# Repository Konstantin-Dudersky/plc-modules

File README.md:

Схемы простейших модулей для подключения к контроллеру по шине I2C.

Схемы разработаны в KiCad.

Документация - см. [docs/plc-modules.pdf]

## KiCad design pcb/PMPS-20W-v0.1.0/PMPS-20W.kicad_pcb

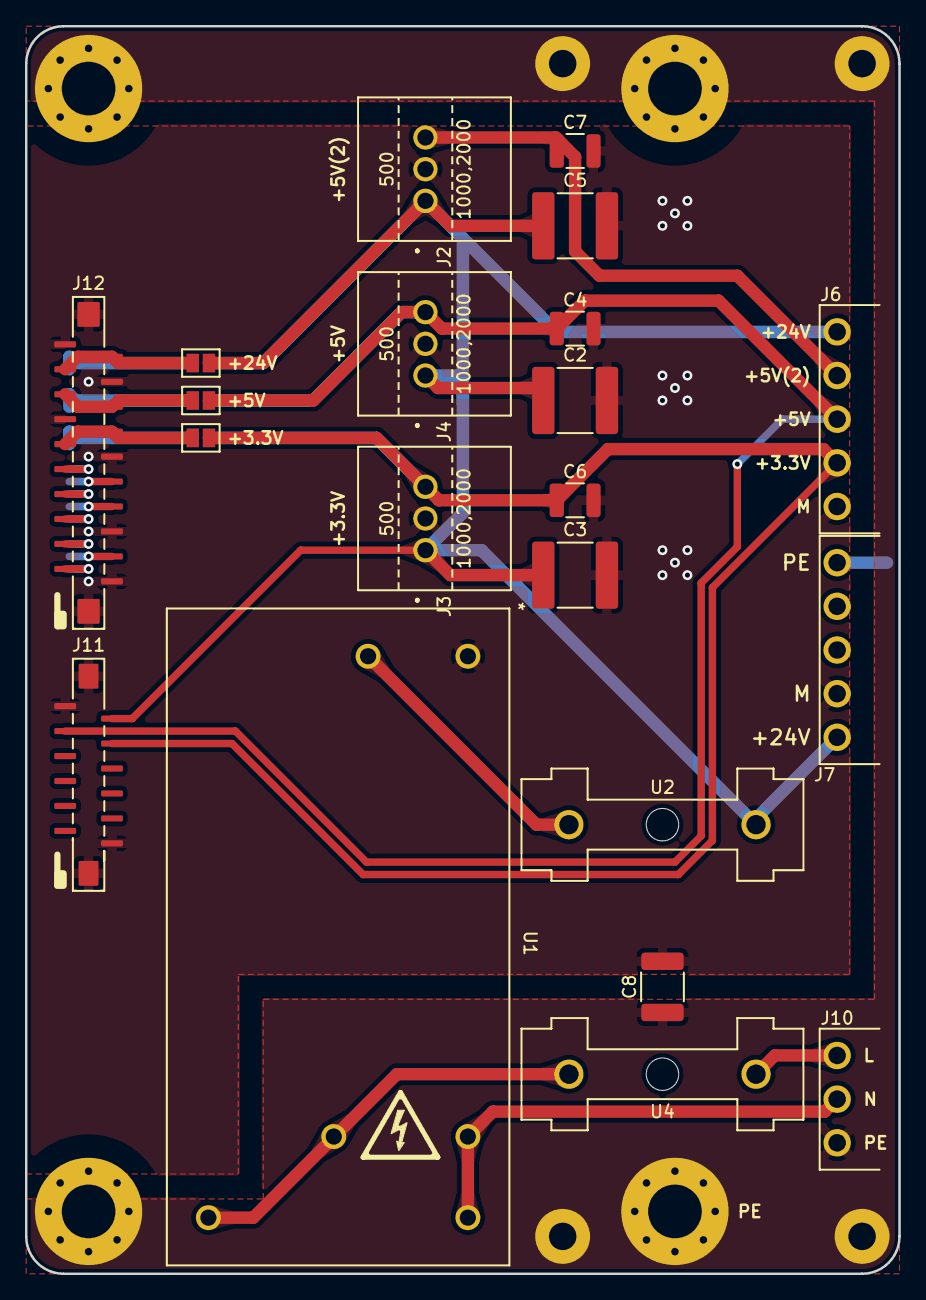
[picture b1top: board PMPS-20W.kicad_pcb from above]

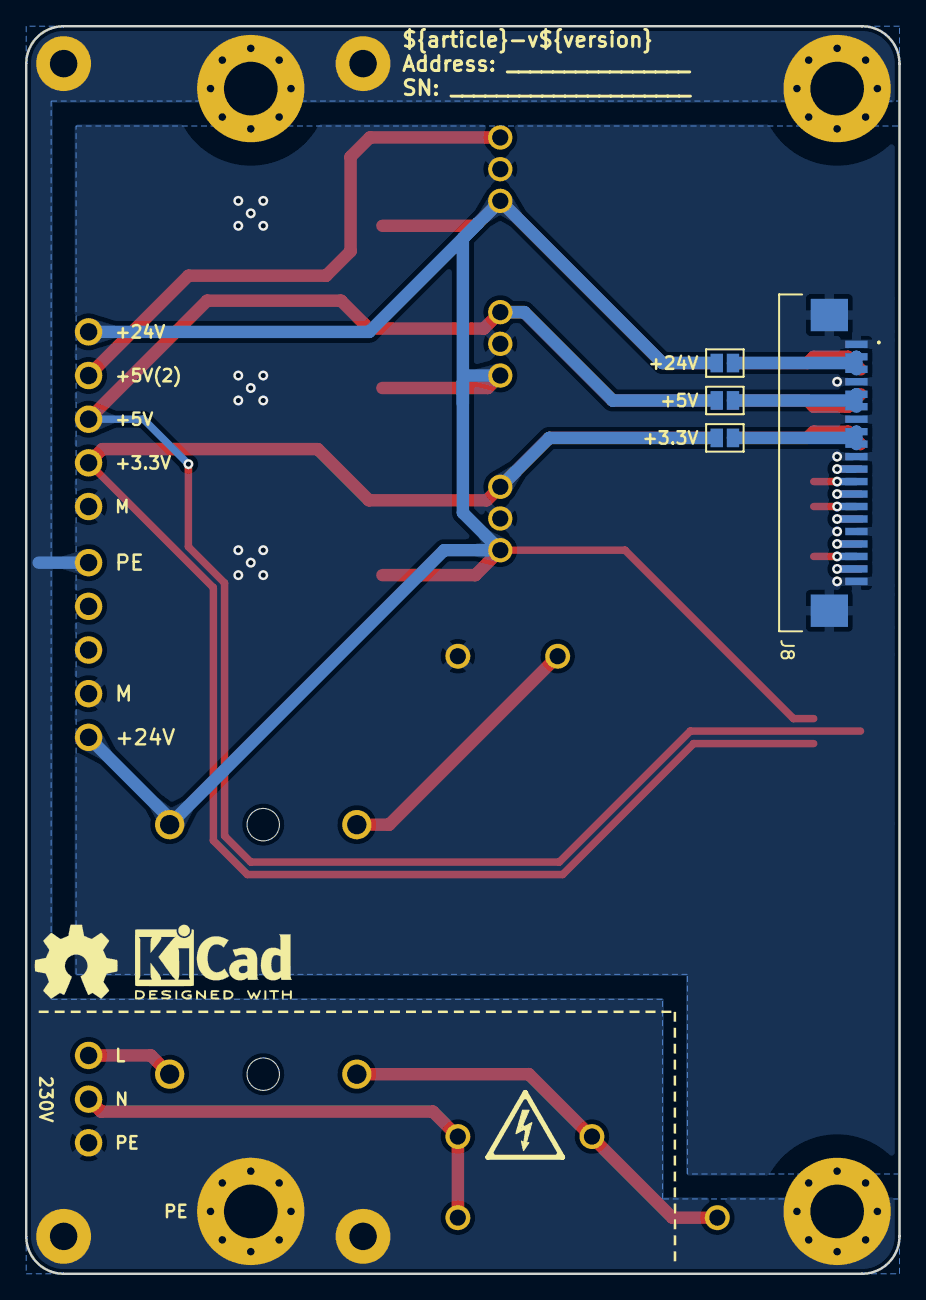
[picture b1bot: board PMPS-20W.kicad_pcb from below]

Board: 2 copper layers, 70.0 x 100.0 mm, 32 parts (6 on the bottom side), 24 nets.

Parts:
C2, C3, C5: 22uF; C_2220_5750Metric
C4, C6, C7: 22uF; C_1210_3225Metric
C8: 4.7nF 2kV; C_1812_4532Metric
H1, H2, H3, H4: M4; MountingHole_4.3mm_M4_Pad_Via
J2, J4: K7805-2000R3
J3: K7803-2000R3; K7805-2000R3
J6, J7: 15EDGRC-3.5-05P
J8: AFA07-S20FCC-00; AFA07S20FCA00
J10: 15EDGRC-3.5-03P
J11: AFA11-S12GLA-00
J12: AFA11-S20GLA-00
JP1, JP2, JP3, JP4, JP5, JP6: SolderJumper_2_Open; SolderJumper-2_P1.3mm_Open_Pad1.0x1.5mm
SP1: PMLED-xx-v0.0.3
U1: IRM-20-24; IRM-XX-24
U2, U4: 64900001039; 649-Series-Holder
kicad_logo: KiCad-Logo2_5mm_SilkScreen
oshw_logo: OSHW-Symbol_6.7x6mm_SilkScreen

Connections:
230V: J10.3, U4.1
+3V3: C6.1, J3.3 (+VO), J6.2, J11.4, JP3.2 (B), JP4.1 (A)
+3V3-IB-back: J8.8, J8.9, JP4.2 (B)
+3V3-IB-front: J12.8, J12.9, JP3.1 (A)
+5V: C4.1, J4.3 (+VO), J6.3, J11.3, JP1.2 (B), JP2.1 (A)
+5V(2): C7.1, J2.3 (+VO), J6.4
+5V-IB-back: J8.5, J8.6, JP2.2 (B)
+5V-IB-front: J12.5, J12.6, JP1.1 (A)
+24V: C2.1, C3.1, C5.1, J2.1 (VIN), J3.1 (VIN), J4.1 (VIN), J6.5, J7.1, J11.2, JP5.2 (B), JP6.1 (A), U2.2
+24V-IB-back: J8.2, J8.3, JP6.2 (B)
+24V-IB-front: J12.2, J12.3, JP5.1 (A)
/IBUS_CAN_GND: J8.13 (Pin_11), J12.13 (Pin_11)
/IBUS_CAN_H: J8.11, J12.11
/IBUS_CAN_L: J8.12 (Pin_11), J12.12 (Pin_11)
/IBUS_I2C_SCL: J8.15 (Pin_11), J12.15 (Pin_11)
/IBUS_I2C_SDA: J8.14 (Pin_11), J12.14 (Pin_11)
/IBUS_RST: J8.19 (Pin_11), J12.19 (Pin_11)
GND_MCU: C2.2, C3.2, C4.2, C5.2, C6.2, C7.2, C8.2, J2.2 (GND), J3.2 (GND), J4.2 (GND), J6.1, J7.2, J8.1, J8.4, J8.7, J8.10, J8.16 (Pin_11), J8.20 (Pin_11), J8.MP1 (Pin_11), J8.MP2 (Pin_11), J11.1, J11.12 (Pin_11), J11.MP1 (Pin_11), J11.MP2 (Pin_11), J12.1, J12.4, J12.7, J12.10, J12.16 (Pin_11), J12.20 (Pin_11), J12.MP1 (Pin_11), J12.MP2 (Pin_11), U1.1 (V-)
N: J10.2, U1.4 (AC/N)
unnamed: J8.17 (Pin_11), J12.17 (Pin_11)
unnamed: J8.18 (Pin_11), J12.18 (Pin_11)
unnamed: U1.3 (AC/L), U4.2
unnamed: U1.2 (V+), U2.1
PE: C8.1, H1.1 (1_1), H2.1 (1_1), H3.1 (1_1), H4.1 (1_1), J7.5, J10.1, SP1.PE (PE_PE)

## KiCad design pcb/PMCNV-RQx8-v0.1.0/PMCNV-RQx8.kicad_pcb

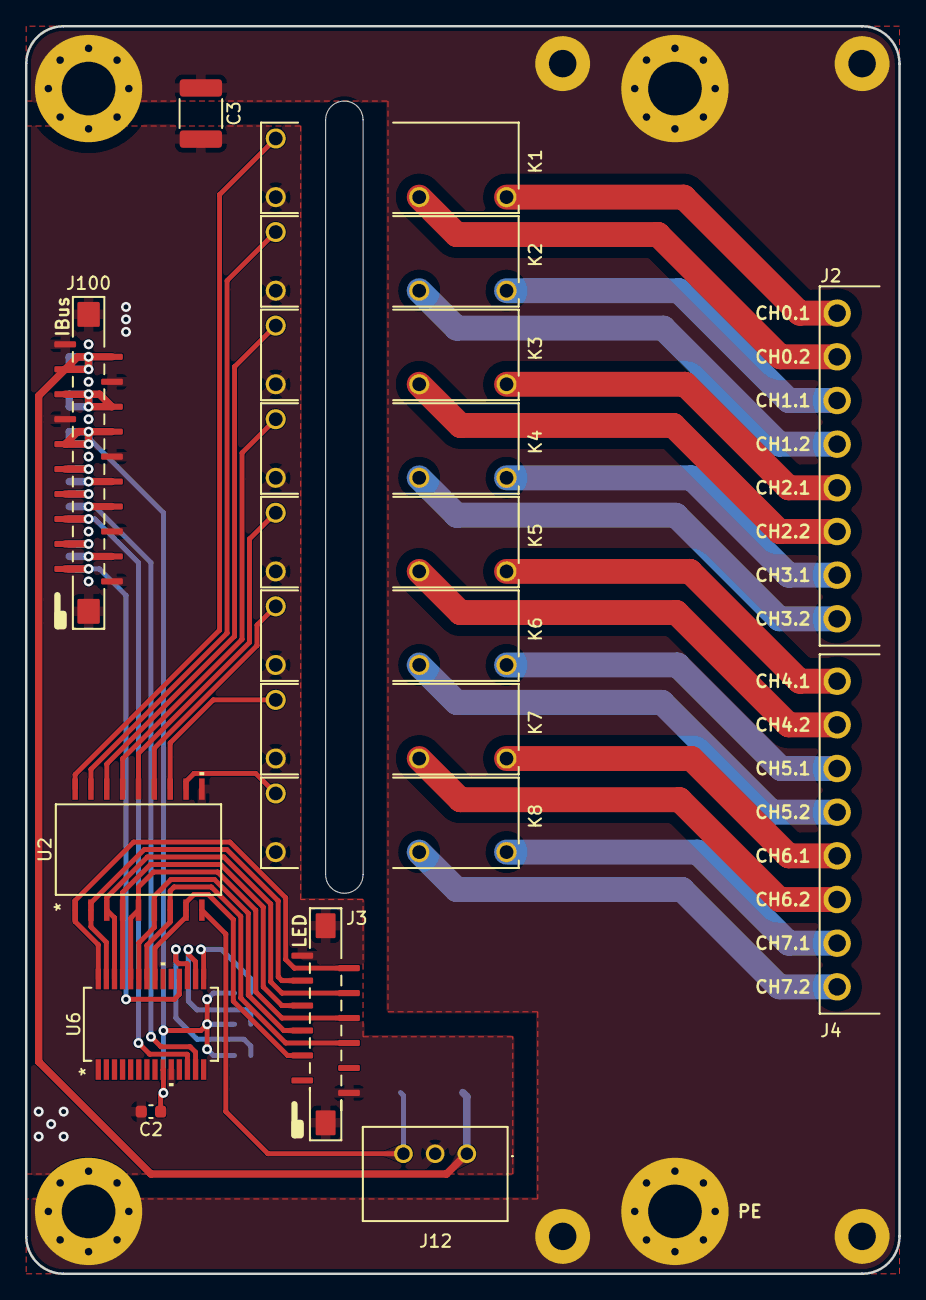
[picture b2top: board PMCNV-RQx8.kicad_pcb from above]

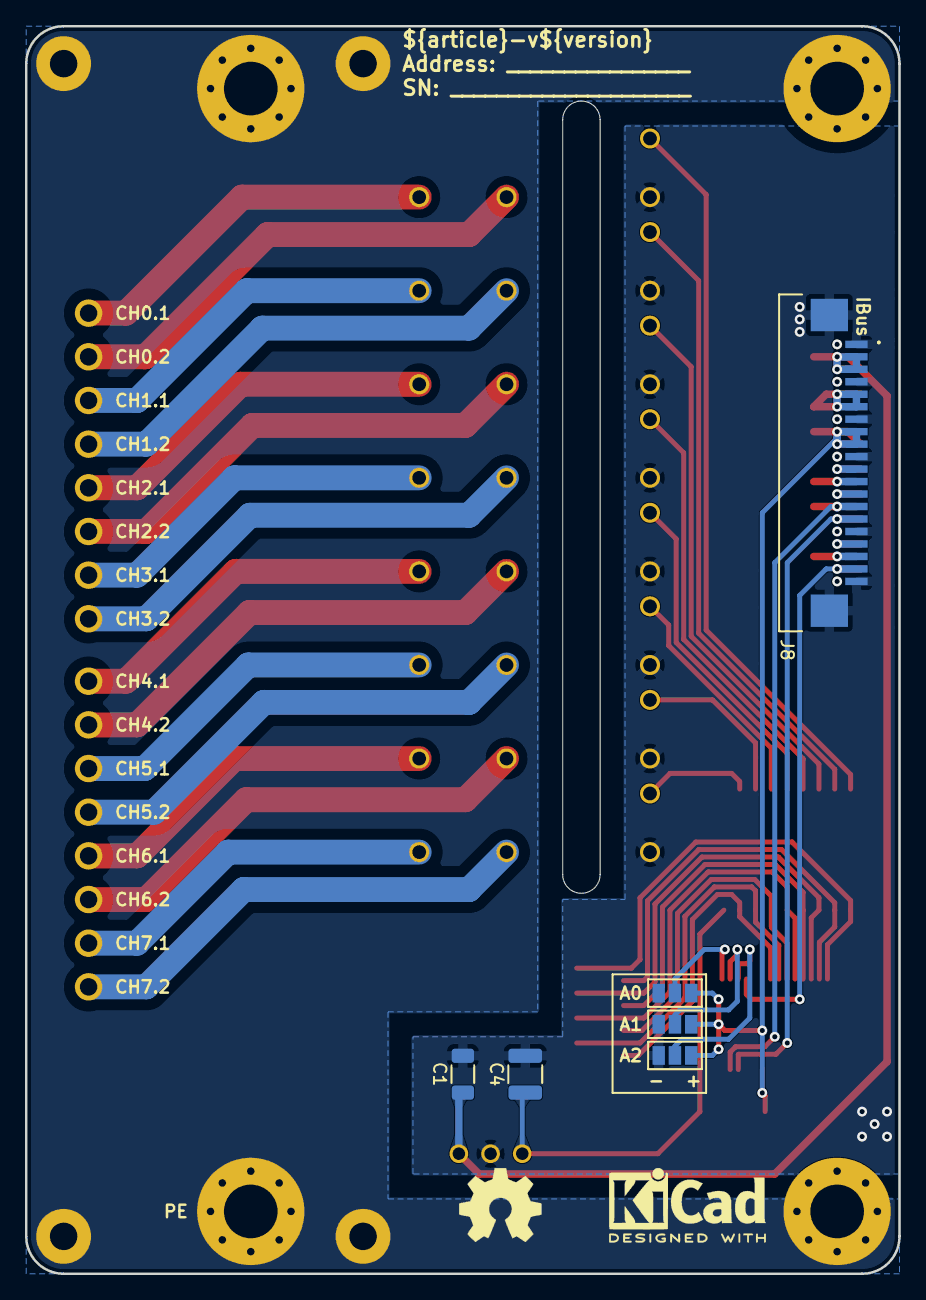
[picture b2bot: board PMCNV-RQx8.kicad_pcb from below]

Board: 2 copper layers, 70.0 x 100.0 mm, 30 parts (9 on the bottom side), 49 nets.

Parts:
C1: 10uF; C_1206_3216Metric
C2: 100nF; C_0603_1608Metric
C3: 4.7nF 2kV; C_1812_4532Metric
C4: 22uF; C_1210_3225Metric
H1, H2, H3, H4: M4; MountingHole_4.3mm_M4_Pad_Via
J2, J4: 15EDGRC-3.5-08P
J3: AFA07-S12FCC-00; AFA11-S12GLA-00
J8: AFA07-S20FCC-00; AFA07S20FCA00
J12: K7805-500R3; K7805500R3
J100: AFA11-S20GLA-00
JP5, JP6, JP7: SolderJumper_3_Open; SolderJumper-3_P1.3mm_Open_Pad1.0x1.5mm
K1, K2, K3, K4, K5, K6, K7, K8: G5NB-1A-E-DC5; G5NB-1A-E_DC12_RELAY_G5NB-1A_DC5_OMR
SP3: PMLED-xx-v0.0.3
U2: TBD62783AFG; SOP18-P-375-1p27_TOS-M
U6: MCP23017_SS; SSOP28_MC_MCH
kicad_logo: KiCad-Logo2_5mm_SilkScreen
oshw_logo: OSHW-Symbol_6.7x6mm_SilkScreen

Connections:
+5V: C4.1, J12.3 (+VO), U2.9 (VCC)
/A0: JP5.2 (C), U6.15 (A0)
/A1: JP6.2 (C), U6.16 (A1)
/A2: JP7.2 (C), U6.17 (A2)
/IBUS_5V: J8.5, J8.6, J100.5, J100.6
/IBUS_CAN_GND: J8.13 (Pin_11), J100.13 (Pin_11)
/IBUS_CAN_H: J8.11, J100.11
/IBUS_CAN_L: J8.12 (Pin_11), J100.12 (Pin_11)
/IBUS_I2C_SCL: J8.15 (Pin_11), J100.15 (Pin_11), U6.12 (SCL)
/IBUS_I2C_SDA: J8.14 (Pin_11), J100.14 (Pin_11), U6.13 (SDA)
/IBUS_RST: J8.19 (Pin_11), J100.19 (Pin_11), U6.18 (~RESET)
/K1: K1.4, U2.18 (O1)
/K1_exp: J3.2, U2.1 (I1), U6.28 (GPA7)
/K2: K2.4, U2.17 (O2)
/K2_exp: J3.3, U2.2 (I2), U6.27 (GPA6)
/K3: K3.4, U2.16 (O3)
/K3_exp: J3.4, U2.3 (I3), U6.26 (GPA5)
/K4: K4.4, U2.15 (O4)
/K4_exp: J3.5, U2.4 (I4), U6.25 (GPA4)
/K5: K5.4, U2.14 (O5)
/K5_exp: J3.6, U2.5 (I5), U6.24 (GPA3)
/K6: K6.4, U2.13 (O6)
/K6_exp: J3.7, U2.6 (I6), U6.23 (GPA2)
/K7: K7.4, U2.12 (O7)
/K7_exp: J3.8, U2.7 (I7), U6.22 (GPA1)
/K8: K8.4, U2.11 (O8)
/K8_exp: J3.9, U2.8 (I8), U6.21 (GPA0)
IBUS_3V3: C2.1, J8.8, J8.9, J100.8, J100.9, JP5.3 (B), JP6.3 (B), JP7.3 (B), U6.9 (VDD)
IBUS_24V: C1.1, J8.2, J8.3, J12.1 (VIN), J100.2, J100.3
IBUS_GND: C1.2, C2.2, C3.2, C4.2, J3.1, J3.12 (Pin_11), J3.MP1 (Pin_11), J3.MP2 (Pin_11), J8.1, J8.4, J8.7, J8.10, J8.16 (Pin_11), J8.20 (Pin_11), J8.MP1 (Pin_11), J8.MP2 (Pin_11), J12.2 (GND), J100.1, J100.4, J100.7, J100.10, J100.16 (Pin_11), J100.20 (Pin_11), J100.MP1 (Pin_11), J100.MP2 (Pin_11), JP5.1 (A), JP6.1 (A), JP7.1 (A), K1.1, K2.1, K3.1, K4.1, K5.1, K6.1, K7.1, K8.1, U2.10 (GND), U6.10 (VSS)
unnamed: J2.1, K4.2
unnamed: J2.2, K4.3
unnamed: J2.3, K3.2
unnamed: J2.4, K3.3
unnamed: J2.5, K2.2
unnamed: J2.6, K2.3
unnamed: J2.7, K1.2
unnamed: J2.8, K1.3
unnamed: J4.1, K8.2
unnamed: J4.2, K8.3
unnamed: J4.3, K7.2
unnamed: J4.4, K7.3
unnamed: J4.5, K6.2
unnamed: J4.6, K6.3
unnamed: J4.7, K5.2
unnamed: J4.8, K5.3
unnamed: J8.17 (Pin_11), J100.17 (Pin_11)
unnamed: J8.18 (Pin_11), J100.18 (Pin_11)
PE: C3.1, H1.1 (1_1), H2.1 (1_1), H3.1 (1_1), H4.1 (1_1), SP3.PE (PE_PE)

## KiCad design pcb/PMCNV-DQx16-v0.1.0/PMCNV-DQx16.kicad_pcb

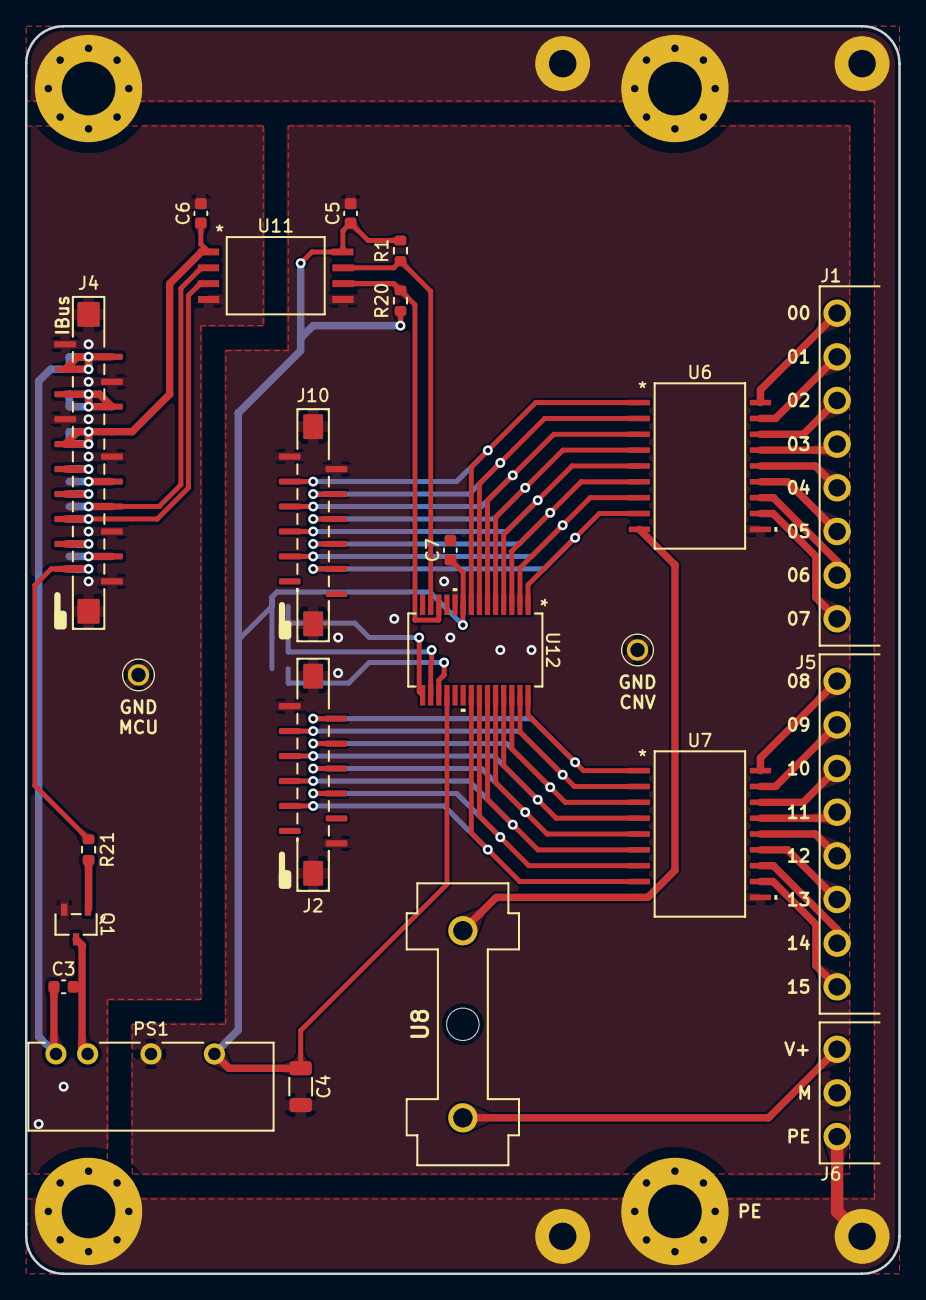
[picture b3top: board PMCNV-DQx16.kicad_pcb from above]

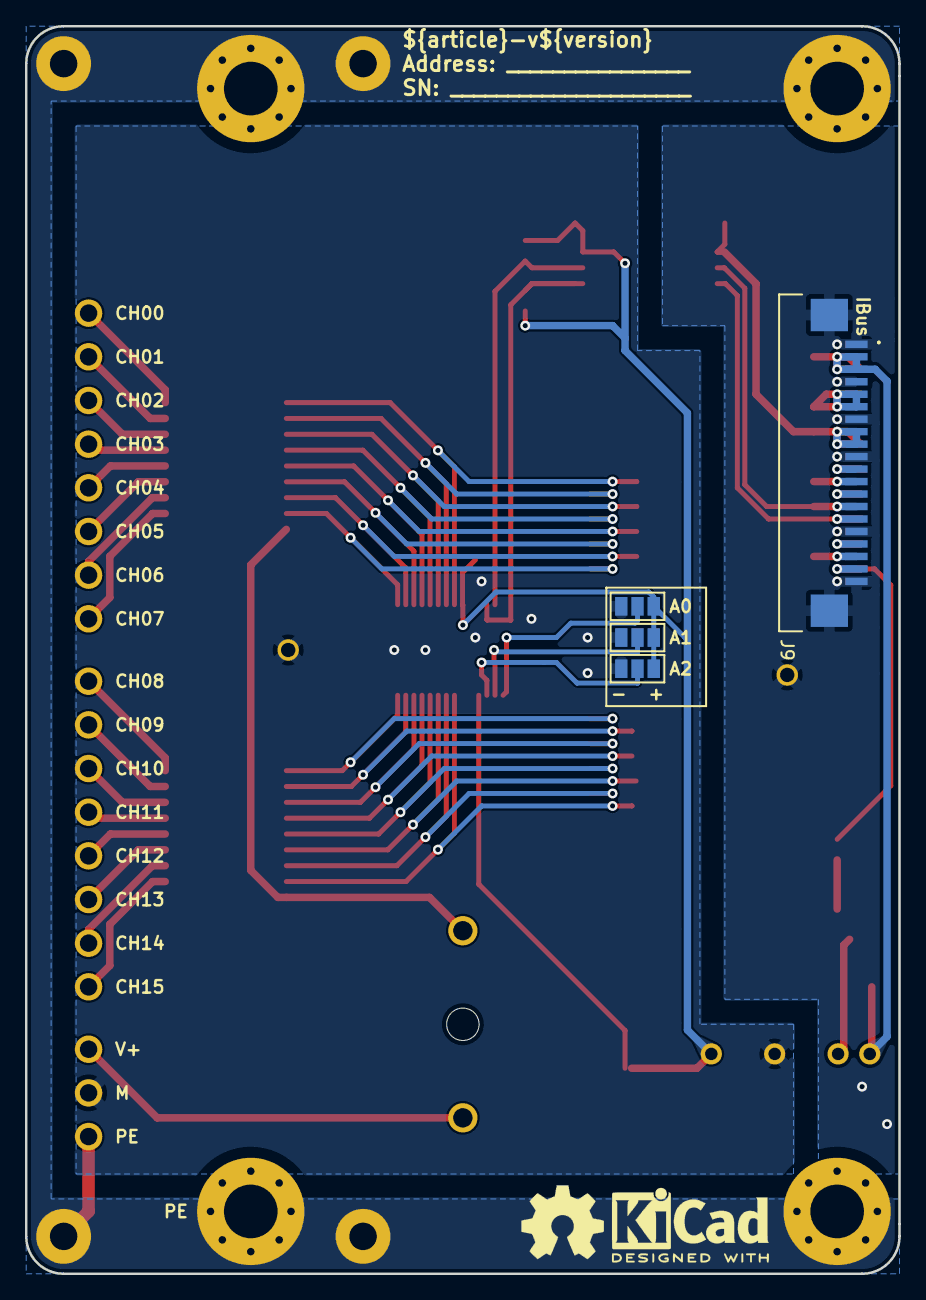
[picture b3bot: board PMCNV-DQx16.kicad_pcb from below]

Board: 2 copper layers, 70.0 x 100.0 mm, 34 parts (6 on the bottom side), 56 nets.

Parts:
C3: 1uF; C_0603_1608Metric
C4: 10uF; C_1206_3216Metric
C5, C6, C7: 100nF; C_0603_1608Metric
H1, H2, H3, H4: M4; MountingHole_4.3mm_M4_Pad_Via
J1, J5: 15EDGRC-3.5-08P
J2, J10: AFA11-S12GLA-00
J4: AFA11-S20GLA-00
J6: 15EDGRC-3.5-03P
J9: AFA07-S20FCC-00; AFA07S20FCA00
JP5, JP6, JP7: SolderJumper_3_Open; SolderJumper-3_P1.3mm_Open_Pad1.0x1.5mm
PS1: 24V/5V; B2405LS-1WR3
Q1: 2N7002K; 2N7002K_ONS
R1, R20: 3k3; R_0603_1608Metric
R21: 100R; R_0603_1608Metric
SP1: PMLED-xx-v0.0.3
U2, U5: 5117
U6, U7: TBD62783AFG; SOP18-P-375-1p27_TOS-M
U8: 64900001039; 649-Series-Holder
U11: CA-IS3021G; SOICW8_CLG
U12: MCP23017_SS; SSOP28_MC_MCH
kicad_logo: KiCad-Logo2_5mm_SilkScreen
oshw_logo: OSHW-Symbol_6.7x6mm_SilkScreen

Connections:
+5V_CNV: C4.1, C5.1, C7.1, JP5.3 (B), JP6.3 (B), JP7.3 (B), PS1.6 (+V), R1.1, R20.1, U11.8 (VDDb), U12.9 (VDD), U12.18 (~RESET)
+V: U6.9 (VCC), U7.9 (VCC), U8.2
/A0: JP5.2 (C), U12.15 (A0)
/A1: JP6.2 (C), U12.16 (A1)
/A2: JP7.2 (C), U12.17 (A2)
/CH00_in: J10.3, U6.1 (I1), U12.8 (GPB7)
/CH01_in: J10.4, U6.2 (I2), U12.7 (GPB6)
/CH02_in: J10.5, U6.3 (I3), U12.6 (GPB5)
/CH03_in: J10.6, U6.4 (I4), U12.5 (GPB4)
/CH04_in: J10.7, U6.5 (I5), U12.4 (GPB3)
/CH05_in: J10.8, U6.6 (I6), U12.3 (GPB2)
/CH06_in: J10.9, U6.7 (I7), U12.2 (GPB1)
/CH07_in: J10.10, U6.8 (I8), U12.1 (GPB0)
/CH08_in: J2.2, U7.1 (I1), U12.28 (GPA7)
/CH09_in: J2.3, U7.2 (I2), U12.27 (GPA6)
/CH10_in: J2.4, U7.3 (I3), U12.26 (GPA5)
/CH11_in: J2.5, U7.4 (I4), U12.25 (GPA4)
/CH12_in: J2.6, U7.5 (I5), U12.24 (GPA3)
/CH13_in: J2.7, U7.6 (I6), U12.23 (GPA2)
/CH14_in: J2.8, U7.7 (I7), U12.22 (GPA1)
/CH15_in: J2.9, U7.8 (I8), U12.21 (GPA0)
/IBUS_5V: J4.5, J4.6, J9.5, J9.6
/IBUS_CAN_GND: J4.13 (Pin_11), J9.13 (Pin_11)
/IBUS_CAN_H: J4.11, J9.11
/IBUS_CAN_L: J4.12 (Pin_11), J9.12 (Pin_11)
/IBUS_I2C_SCL: J4.15 (Pin_11), J9.15 (Pin_11), U11.3 (SCLa)
/IBUS_I2C_SDA: J4.14 (Pin_11), J9.14 (Pin_11), U11.2 (SDAa)
/IBUS_RST: J4.19 (Pin_11), J9.19 (Pin_11), R21.1
/SCL_CNV: R20.2, U11.6 (SCLb), U12.12 (SCK)
/SDA_CNV: R1.2, U11.7 (SDAb), U12.13 (SI)
/a.0_out: J1.8, U6.18 (O1)
/a.1_out: J1.7, U6.17 (O2)
/a.2_out: J1.6, U6.16 (O3)
/a.3_out: J1.5, U6.15 (O4)
/a.4_out: J1.4, U6.14 (O5)
/a.5_out: J1.3, U6.13 (O6)
/a.6_out: J1.2, U6.12 (O7)
/a.7_out: J1.1, U6.11 (O8)
/b.0_out: J5.8, U7.18 (O1)
/b.1_out: J5.7, U7.17 (O2)
/b.2_out: J5.6, U7.16 (O3)
/b.3_out: J5.5, U7.15 (O4)
/b.4_out: J5.4, U7.14 (O5)
/b.5_out: J5.3, U7.13 (O6)
/b.6_out: J5.2, U7.12 (O7)
/b.7_out: J5.1, U7.11 (O8)
GND_CNV: C4.2, C5.2, C7.2, J2.1, J2.12 (Pin_11), J2.MP1 (Pin_11), J2.MP2 (Pin_11), J6.2, J10.1, J10.2, J10.MP1 (Pin_11), J10.MP2 (Pin_11), JP5.1 (A), JP6.1 (A), JP7.1 (A), PS1.4 (0V), U5.1, U6.10 (GND), U7.10 (GND), U11.5 (GNDb), U12.10 (VSS)
IBUS_3V3: C6.1, J4.8, J4.9, J9.8, J9.9, U11.1 (VDDa)
IBUS_24V: C3.1, J4.2, J4.3, J9.2, J9.3, PS1.1 (Vin)
IBUS_GND: C6.2, J4.1, J4.4, J4.7, J4.10, J4.16 (Pin_11), J4.20 (Pin_11), J4.MP1 (Pin_11), J4.MP2 (Pin_11), J9.1, J9.4, J9.7, J9.10, J9.16 (Pin_11), J9.20 (Pin_11), J9.MP1 (Pin_11), J9.MP2 (Pin_11), Q1.2 (S), U2.1, U11.4 (GNDa)
unnamed: J4.17 (Pin_11), J9.17 (Pin_11)
unnamed: J4.18 (Pin_11), J9.18 (Pin_11)
unnamed: J6.3, U8.1
unnamed: C3.2, PS1.2 (GND), Q1.3 (D)
unnamed: Q1.1 (G), R21.2
PE: H1.1 (1_1), H2.1 (1_1), H3.1 (1_1), H4.1 (1_1), J6.1, SP1.PE (PE_PE)

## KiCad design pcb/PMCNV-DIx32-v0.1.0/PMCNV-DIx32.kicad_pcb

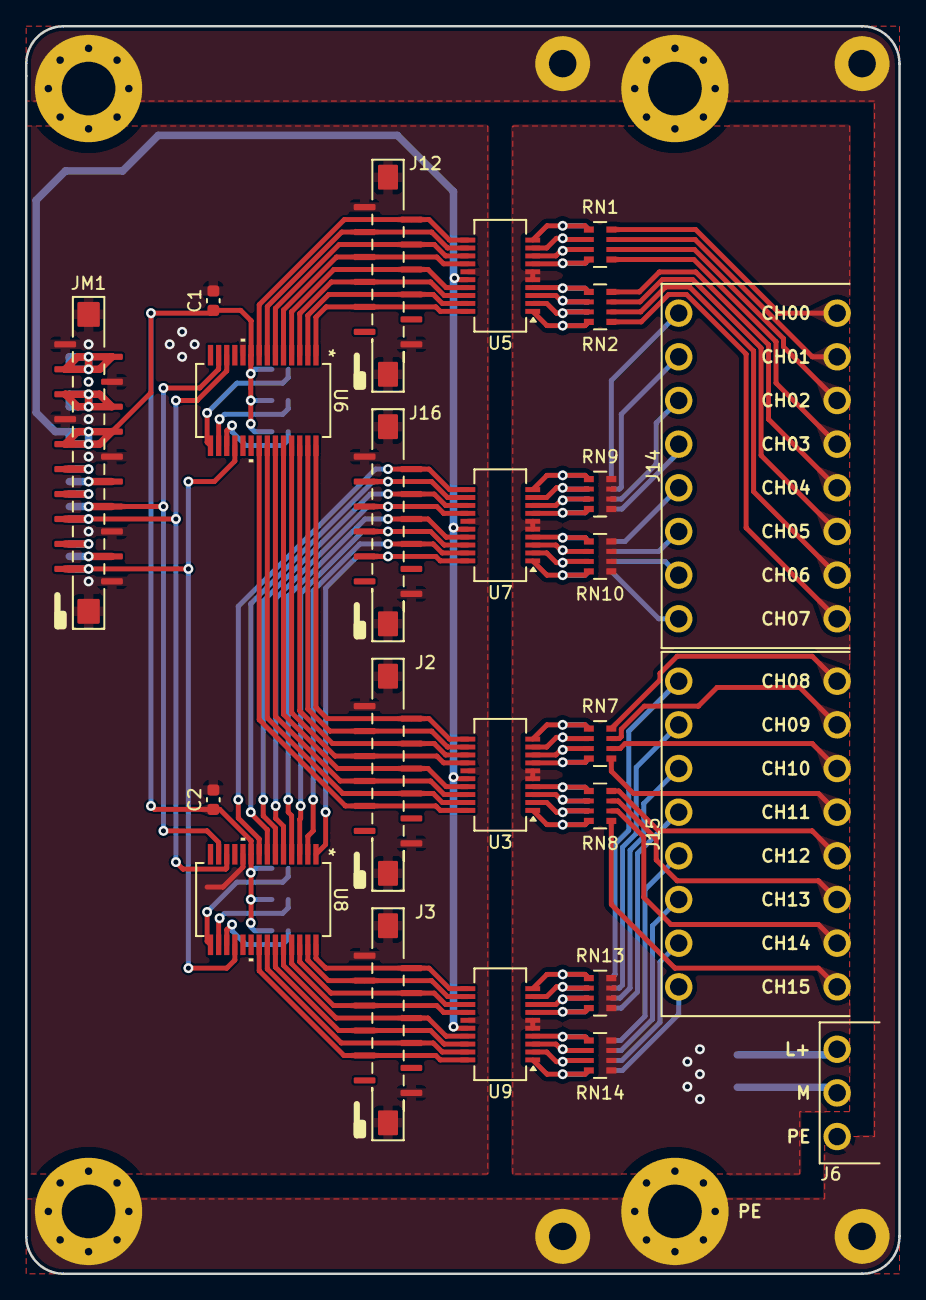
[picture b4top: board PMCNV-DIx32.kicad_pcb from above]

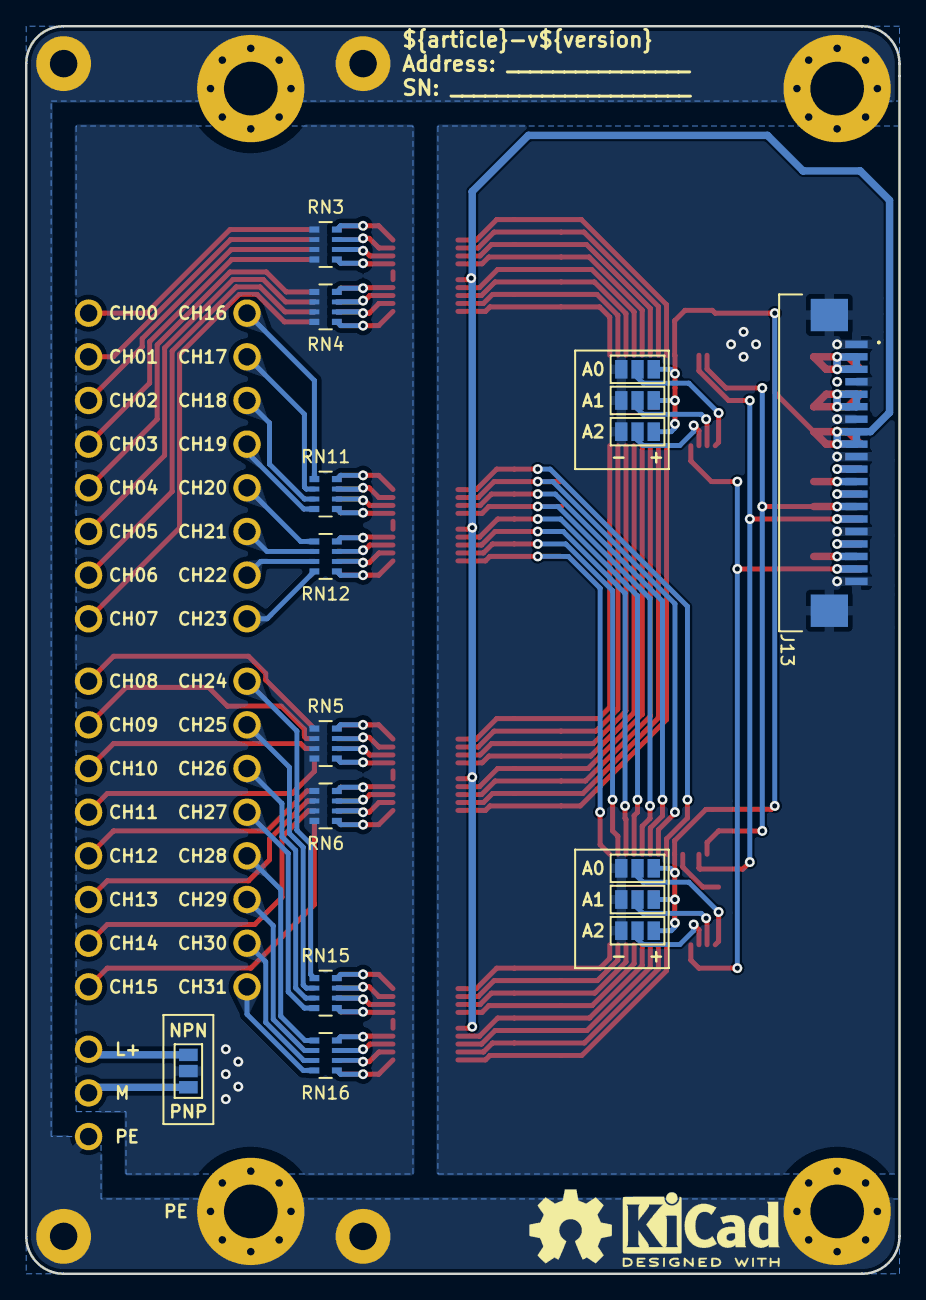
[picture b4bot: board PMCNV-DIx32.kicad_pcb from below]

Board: 2 copper layers, 70.0 x 100.0 mm, 47 parts (18 on the bottom side), 118 nets.

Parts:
C1, C2: 100nF; C_0603_1608Metric
H1, H2, H3, H4: M4; MountingHole_4.3mm_M4_Pad_Via
J2, J3, J12, J16: AFA07-S12FCC-00; AFA11-S12GLA-00
J6: 15EDGRC-3.5-05P; 15EDGRC-3.5-03P
J13: AFA07-S20FCC-00; AFA07S20FCA00
J14, J15: 15EDGRH-3.5-16P
JM1: AFA07-S20FCC-00; AFA11-S20GLA-00
JP5, JP6, JP7, JP8, JP9, JP10, JP11: SolderJumper_3_Open; SolderJumper-3_P1.3mm_Open_Pad1.0x1.5mm
RN1, RN2, RN7, RN8, RN11, RN12, RN15, RN16: 2k7; R_Array_Convex_4x0603
RN3, RN4, RN5, RN6, RN9, RN10, RN13, RN14: 750R; R_Array_Convex_4x0603
SP1: PMLED-xx-v0.0.3
U3, U5, U7, U9: CA-IS3980P; SSOP-20_3.9x8.7mm_P0.635mm
U6, U8: MCP23017_SS; SSOP28_MC_MCH
kicad_logo: KiCad-Logo2_5mm_SilkScreen
oshw_logo: OSHW-Symbol_6.7x6mm_SilkScreen

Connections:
/A0_0: JP5.2 (C), U6.15 (A0)
/A0_1: JP8.2 (C), U8.15 (A0)
/A1_0: JP6.2 (C), U6.16 (A1)
/A1_1: JP9.2 (C), U8.16 (A1)
/A2_0: JP7.2 (C), U6.17 (A2)
/A2_1: JP11.2 (C), U8.17 (A2)
/CH00: J12.2, U5.11 (B8), U6.8 (GPB7)
/CH00_div: RN1.1 (R1.1), RN3.4 (R4.1), U5.10 (A8)
/CH00_in: J14.8, RN1.8 (R1.2)
/CH01: J12.3, U5.12 (B7), U6.7 (GPB6)
/CH01_div: RN1.2 (R2.1), RN3.3 (R3.1), U5.9 (A7)
/CH01_in: J14.7, RN1.7 (R2.2)
/CH02: J12.4, U5.13 (B6), U6.6 (GPB5)
/CH02_div: RN1.3 (R3.1), RN3.2 (R2.1), U5.8 (A6)
/CH02_in: J14.6, RN1.6 (R3.2)
/CH03: J12.5, U5.14 (B5), U6.5 (GPB4)
/CH03_div: RN1.4 (R4.1), RN3.1 (R1.1), U5.7 (A5)
/CH03_in: J14.5, RN1.5 (R4.2)
/CH04: J12.6, U5.17 (B4), U6.4 (GPB3)
/CH04_div: RN2.1 (R1.1), RN4.4 (R4.1), U5.4 (A4)
/CH04_in: J14.4, RN2.8 (R1.2)
/CH05: J12.7, U5.18 (B3), U6.3 (GPB2)
/CH05_div: RN2.2 (R2.1), RN4.3 (R3.1), U5.3 (A3)
/CH05_in: J14.3, RN2.7 (R2.2)
/CH06: J12.8, U5.19 (B2), U6.2 (GPB1)
/CH06_div: RN2.3 (R3.1), RN4.2 (R2.1), U5.2 (A2)
/CH06_in: J14.2, RN2.6 (R3.2)
/CH07: J12.9, U5.20 (B1), U6.1 (GPB0)
/CH07_div: RN2.4 (R4.1), RN4.1 (R1.1), U5.1 (A1)
/CH07_in: J14.1, RN2.5 (R4.2)
/CH08: J2.2, U3.11 (B8), U6.28 (GPA7)
/CH08_div: RN5.4 (R4.1), RN7.1 (R1.1), U3.10 (A8)
/CH08_in: J15.8, RN7.8 (R1.2)
/CH09: J2.3, U3.12 (B7), U6.27 (GPA6)
/CH09_div: RN5.3 (R3.1), RN7.2 (R2.1), U3.9 (A7)
/CH09_in: J15.7, RN7.7 (R2.2)
/CH10: J2.4, U3.13 (B6), U6.26 (GPA5)
/CH10_div: RN5.2 (R2.1), RN7.3 (R3.1), U3.8 (A6)
/CH10_in: J15.6, RN7.6 (R3.2)
/CH11: J2.5, U3.14 (B5), U6.25 (GPA4)
/CH11_div: RN5.1 (R1.1), RN7.4 (R4.1), U3.7 (A5)
/CH11_in: J15.5, RN7.5 (R4.2)
/CH12: J2.6, U3.17 (B4), U6.24 (GPA3)
/CH12_div: RN6.4 (R4.1), RN8.1 (R1.1), U3.4 (A4)
/CH12_in: J15.4, RN8.8 (R1.2)
/CH13: J2.7, U3.18 (B3), U6.23 (GPA2)
/CH13_div: RN6.3 (R3.1), RN8.2 (R2.1), U3.3 (A3)
/CH13_in: J15.3, RN8.7 (R2.2)
/CH14: J2.8, U3.19 (B2), U6.22 (GPA1)
/CH14_div: RN6.2 (R2.1), RN8.3 (R3.1), U3.2 (A2)
/CH14_in: J15.2, RN8.6 (R3.2)
/CH15: J2.9, U3.20 (B1), U6.21 (GPA0)
/CH15_div: RN6.1 (R1.1), RN8.4 (R4.1), U3.1 (A1)
/CH15_in: J15.1, RN8.5 (R4.2)
/CH16: J16.2, U7.11 (B8), U8.8 (GPB7)
/CH16_div: RN9.1 (R1.1), RN11.4 (R4.1), U7.10 (A8)
/CH16_in: J14.16, RN11.5 (R4.2)
/CH17: J16.3, U7.12 (B7), U8.7 (GPB6)
/CH17_div: RN9.2 (R2.1), RN11.3 (R3.1), U7.9 (A7)
/CH17_in: J14.15, RN11.6 (R3.2)
/CH18: J16.4, U7.13 (B6), U8.6 (GPB5)
/CH18_div: RN9.3 (R3.1), RN11.2 (R2.1), U7.8 (A6)
/CH18_in: J14.14, RN11.7 (R2.2)
/CH19: J16.5, U7.14 (B5), U8.5 (GPB4)
/CH19_div: RN9.4 (R4.1), RN11.1 (R1.1), U7.7 (A5)
/CH19_in: J14.13, RN11.8 (R1.2)
/CH20: J16.6, U7.17 (B4), U8.4 (GPB3)
/CH20_div: RN10.1 (R1.1), RN12.4 (R4.1), U7.4 (A4)
/CH20_in: J14.12, RN12.5 (R4.2)
/CH21: J16.7, U7.18 (B3), U8.3 (GPB2)
/CH21_div: RN10.2 (R2.1), RN12.3 (R3.1), U7.3 (A3)
/CH21_in: J14.11, RN12.6 (R3.2)
/CH22: J16.8, U7.19 (B2), U8.2 (GPB1)
/CH22_div: RN10.3 (R3.1), RN12.2 (R2.1), U7.2 (A2)
/CH22_in: J14.10, RN12.7 (R2.2)
/CH23: J16.9, U7.20 (B1), U8.1 (GPB0)
/CH23_div: RN10.4 (R4.1), RN12.1 (R1.1), U7.1 (A1)
/CH23_in: J14.9, RN12.8 (R1.2)
/CH24: J3.2, U8.28 (GPA7), U9.11 (B8)
/CH24_div: RN13.1 (R1.1), RN15.4 (R4.1), U9.10 (A8)
/CH24_in: J15.16, RN15.5 (R4.2)
/CH25: J3.3, U8.27 (GPA6), U9.12 (B7)
/CH25_div: RN13.2 (R2.1), RN15.3 (R3.1), U9.9 (A7)
/CH25_in: J15.15, RN15.6 (R3.2)
/CH26: J3.4, U8.26 (GPA5), U9.13 (B6)
/CH26_div: RN13.3 (R3.1), RN15.2 (R2.1), U9.8 (A6)
/CH26_in: J15.14, RN15.7 (R2.2)
/CH27: J3.5, U8.25 (GPA4), U9.14 (B5)
/CH27_div: RN13.4 (R4.1), RN15.1 (R1.1), U9.7 (A5)
/CH27_in: J15.13, RN15.8 (R1.2)
/CH28: J3.6, U8.24 (GPA3), U9.17 (B4)
/CH28_div: RN14.1 (R1.1), RN16.4 (R4.1), U9.4 (A4)
/CH28_in: J15.12, RN16.5 (R4.2)
/CH29: J3.7, U8.23 (GPA2), U9.18 (B3)
/CH29_div: RN14.2 (R2.1), RN16.3 (R3.1), U9.3 (A3)
/CH29_in: J15.11, RN16.6 (R3.2)
/CH30: J3.8, U8.22 (GPA1), U9.19 (B2)
/CH30_div: RN14.3 (R3.1), RN16.2 (R2.1), U9.2 (A2)
/CH30_in: J15.10, RN16.7 (R2.2)
/CH31: J3.9, U8.21 (GPA0), U9.20 (B1)
/CH31_div: RN14.4 (R4.1), RN16.1 (R1.1), U9.1 (A1)
/CH31_in: J15.9, RN16.8 (R1.2)
/COM_CNV: JP10.2 (C), RN3.5 (R4.2), RN3.6 (R3.2), RN3.7 (R2.2), RN3.8 (R1.2), RN4.5 (R4.2), RN4.6 (R3.2), RN4.7 (R2.2), RN4.8 (R1.2), RN5.5 (R4.2), RN5.6 (R3.2), RN5.7 (R2.2), RN5.8 (R1.2), RN6.5 (R4.2), RN6.6 (R3.2), RN6.7 (R2.2), RN6.8 (R1.2), RN9.5 (R4.2), RN9.6 (R3.2), RN9.7 (R2.2), RN9.8 (R1.2), RN10.5 (R4.2), RN10.6 (R3.2), RN10.7 (R2.2), RN10.8 (R1.2), RN13.5 (R4.2), RN13.6 (R3.2), RN13.7 (R2.2), RN13.8 (R1.2), RN14.5 (R4.2), RN14.6 (R3.2), RN14.7 (R2.2), RN14.8 (R1.2), U3.5 (COM), U3.6 (COM), U5.5 (COM), U5.6 (COM), U7.5 (COM), U7.6 (COM), U9.5 (COM), U9.6 (COM)
/IBUS_5V: J13.5, J13.6, JM1.5, JM1.6
/IBUS_24V: J13.2, J13.3, JM1.2, JM1.3
/IBUS_CAN_GND: J13.13 (Pin_11), JM1.13 (Pin_11)
/IBUS_CAN_H: J13.11, JM1.11
/IBUS_CAN_L: J13.12 (Pin_11), JM1.12 (Pin_11)
/IBUS_I2C_SCL: J13.15 (Pin_11), JM1.15 (Pin_11), U6.12 (SCL), U8.12 (SCL)
/IBUS_I2C_SDA: J13.14 (Pin_11), JM1.14 (Pin_11), U6.13 (SDA), U8.13 (SDA)
/IBUS_RST: J13.19 (Pin_11), JM1.19 (Pin_11), U6.18 (~RESET), U8.18 (~RESET)
GND_CNV: J6.2, JP10.1 (A)
IBUS_3V3: C1.1, C2.1, J13.8, J13.9, JM1.8, JM1.9, JP5.3 (B), JP6.3 (B), JP7.3 (B), JP8.3 (B), JP9.3 (B), JP11.3 (B), U3.16 (VDD), U5.16 (VDD), U6.9 (VDD), U7.16 (VDD), U8.9 (VDD), U9.16 (VDD)
IBUS_GND: C1.2, C2.2, J2.1, J2.12 (Pin_11), J2.MP1 (Pin_11), J2.MP2 (Pin_11), J3.1, J3.12 (Pin_11), J3.MP1 (Pin_11), J3.MP2 (Pin_11), J12.1, J12.12 (Pin_11), J12.MP1 (Pin_11), J12.MP2 (Pin_11), J13.1, J13.4, J13.7, J13.10, J13.16 (Pin_11), J13.20 (Pin_11), J13.MP1 (Pin_11), J13.MP2 (Pin_11), J16.1, J16.12 (Pin_11), J16.MP1 (Pin_11), J16.MP2 (Pin_11), JM1.1, JM1.4, JM1.7, JM1.10, JM1.16 (Pin_11), JM1.20 (Pin_11), JM1.MP1 (Pin_11), JM1.MP2 (Pin_11), JP5.1 (A), JP6.1 (A), JP7.1 (A), JP8.1 (A), JP9.1 (A), JP11.1 (A), U3.15 (GND), U5.15 (GND), U6.10 (VSS), U7.15 (GND), U8.10 (VSS), U9.15 (GND)
L+_CNV: J6.3, JP10.3 (B)
unnamed: J13.17 (Pin_11), JM1.17 (Pin_11)
unnamed: J13.18 (Pin_11), JM1.18 (Pin_11)
PE: H1.1 (1_1), H2.1 (1_1), H3.1 (1_1), H4.1 (1_1), J6.1, SP1.PE (PE_PE)

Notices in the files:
parts and their libraries:
COPYRIGHT: Copyright (C) 2023 Ultra Librarian. All rights reserved.
